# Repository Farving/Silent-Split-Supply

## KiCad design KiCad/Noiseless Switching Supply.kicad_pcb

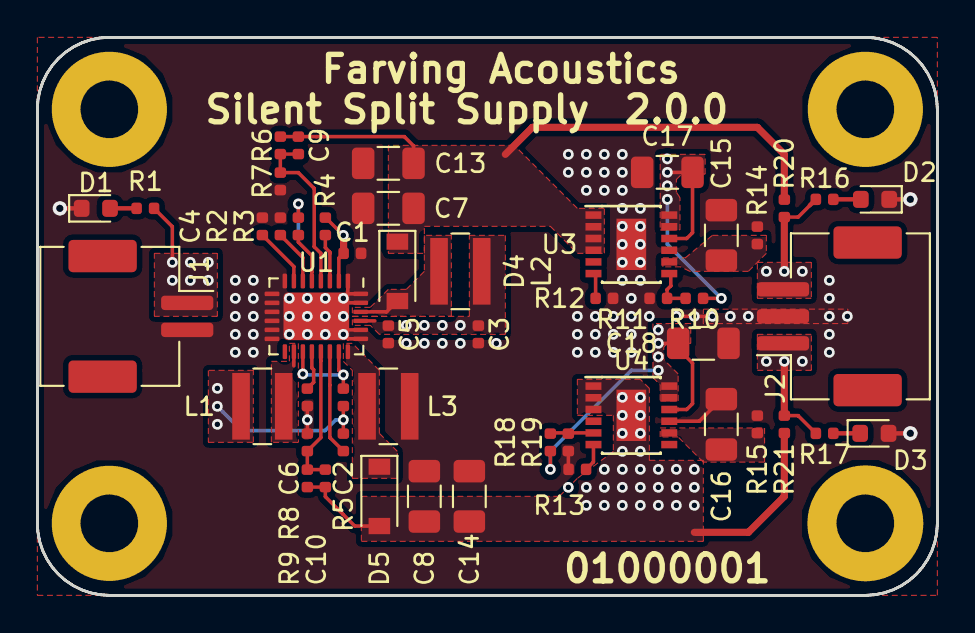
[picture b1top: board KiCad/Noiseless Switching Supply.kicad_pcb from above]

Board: 2 copper layers, 50.0 x 31.0 mm, 51 parts (0 on the bottom side), 27 nets.

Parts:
C1, C2: 1uF; C_0402_1005Metric
C3, C5: 2.2uF; C_0402_1005Metric
C4, C6: 100n; C_0402_1005Metric
C7, C8, C13, C14: 10u; C_1206_3216Metric
C9, C10: 10p; C_0402_1005Metric
C15, C16: 1u; C_1206_3216Metric
C17, C18: 10uF; C_1206_3216Metric
D1, D2, D3: LED_Small; LED_0603_1608Metric
D4, D5: D_Small; D_SOD-123
J1: JST S2B-ZR-SMA4-TF; JST_ZE_SM02B-ZESS-TBT_1x02-1MP_P1.50mm_Horizontal
J2: JST S3B-ZR-SMA4-TF; JST_ZE_SM03B-ZESS-TBT_1x03-1MP_P1.50mm_Horizontal
L1, L2, L3: 10u; L_Wuerth_MAPI-4030
PCB1: Board_Module; PCB_Board_50x31
R1, R16, R17: 1k; R_0402_1005Metric
R2: 82k; R_0402_1005Metric
R3, R4, R5: 100k; R_0402_1005Metric
R6, R9: 390k; R_0402_1005Metric
R7, R8, R11, R18: 18k; R_0402_1005Metric
R10, R19: 750k; R_0402_1005Metric
R12, R13, R20, R21: 0R; R_0402_1005Metric
R14, R15: 150k; R_0402_1005Metric
U1: LT8471; QFN-28-1EP_4x5mm_P0.5mm_EP2.65x3.65mm
U3: LT3045; MSOP-12-1EP_3x4mm_P0.65mm_EP1.65x2.85mm
U4: LT3094; MSOP-12-1EP_3x4mm_P0.65mm_EP1.65x2.85mm

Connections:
+15V: C17.1, J2.3, R10.1, R16.1, R20.1, U3.10, U3.11, U3.12
-15V: C18.2, J2.1, R17.2, R19.2, R21.1, U4.10, U4.11, U4.12
/VIN: C1.1, C2.1, C3.1, C5.1, J1.1, L1.1, L2.1, R1.1, R3.2, R4.2, R5.2, U1.2, U1.25
GND: C1.2, C3.2, C4.2, C5.2, C6.2, C7.2, C8.1, C13.2, C14.1, C15.2, C16.1, C17.2, C18.1, D1.1, D2.1, D3.2, J1.2, J2.2, L3.2, R2.2, R7.2, R8.1, R11.2, R12.2, R13.1, R14.2, R15.1, R18.1, U1.1, U1.8, U1.9, U1.10, U1.11, U1.12, U1.13, U1.14, U1.23, U1.24, U1.27, U1.28, U1.29, U3.9, U3.13, U4.9
unnamed: C2.2, U1.17, U1.21
unnamed: C4.1, U1.7
unnamed: C6.1, U1.18
unnamed: C9.2, R6.2, R7.1, U1.4
unnamed: C10.1, R8.2, R9.1, U1.19
unnamed: C15.1, R14.1, U3.8
unnamed: C16.2, R15.2, U4.8
unnamed: D1.2, R1.2
unnamed: D2.2, R16.2
unnamed: D3.1, R17.1
unnamed: D4.2, L2.2, U1.26
unnamed: D5.1, L3.1, U1.22
unnamed: L1.2, U1.16
unnamed: R2.1, U1.6
unnamed: R3.1, U1.5
unnamed: R4.1, U1.3
unnamed: R5.1, U1.20
unnamed: R10.2, R11.1, U3.7
unnamed: R12.1, U3.6
unnamed: R13.2, U4.6
unnamed: R18.2, R19.1, U4.5
VCC: C7.1, C9.1, C13.1, D4.1, R6.1, R20.2, U3.1, U3.2, U3.3, U3.4
VEE: C8.2, C10.2, C14.2, D5.2, R9.2, R21.2, U4.1, U4.2, U4.3, U4.13

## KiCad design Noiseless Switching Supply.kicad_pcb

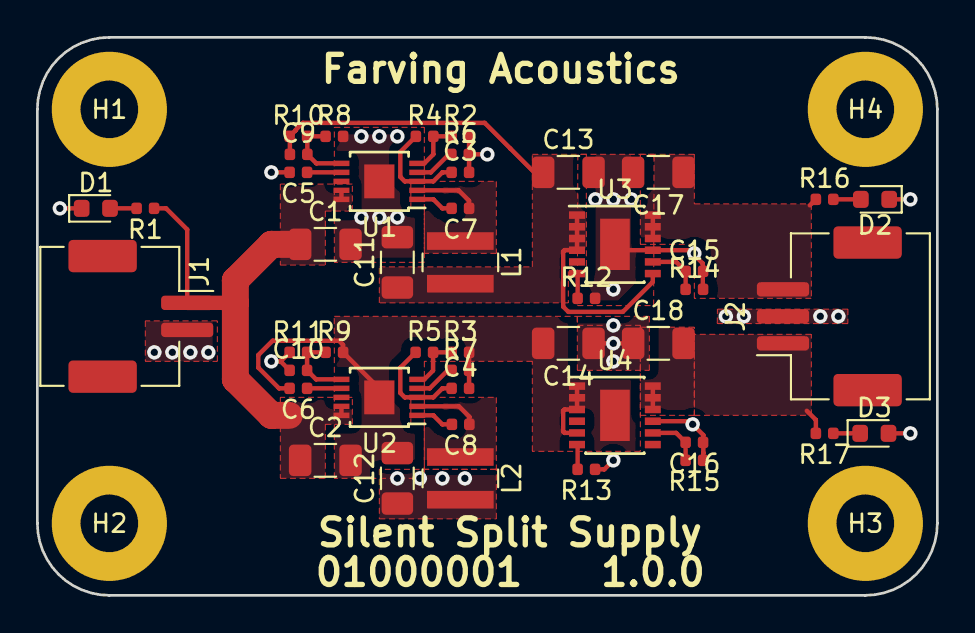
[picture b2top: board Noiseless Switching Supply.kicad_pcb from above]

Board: 2 copper layers, 50.0 x 31.0 mm, 50 parts (0 on the bottom side), 27 nets.

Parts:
C1, C2, C13, C14: 4.7uF; C_1206_3216Metric
C3, C4: 1uF; C_0402_1005Metric
C5, C6: 10nF; C_0402_1005Metric
C7, C8, C9, C10: 100nF; C_0402_1005Metric
C11, C12: 22uF; C_1206_3216Metric
C15, C16: 470nF; C_0402_1005Metric
C17, C18: 10uF; C_1206_3216Metric
D1, D2, D3: LED_Small; LED_0603_1608Metric
H1, H2, H3, H4: MountingHole_Pad; MountingHole_3.2mm_M3_Pad
J1: JST S2B-ZR-SMA4-TF; JST_ZE_SM02B-ZESS-TBT_1x02-1MP_P1.50mm_Horizontal
J2: JST S3B-ZR-SMA4-TF; JST_ZE_SM03B-ZESS-TBT_1x03-1MP_P1.50mm_Horizontal
L1, L2: L; L_Wuerth_MAPI-4020
R1, R16, R17: 1k; R_0402_1005Metric
R2, R3, R12, R13: 0R; R_0402_1005Metric
R4, R5: DNP; R_0402_1005Metric
R6, R7: 40.2k; R_0402_1005Metric
R8, R9, R10, R11: R_Small; R_0402_1005Metric
R14, R15: 150k; R_0402_1005Metric
U1, U2: LT8607; MSOP-10-1EP_3x3mm_P0.5mm_EP1.68x1.88mm
U3: LT3045; MSOP-12-1EP_3x4mm_P0.65mm_EP1.65x2.85mm
U4: LT3094; MSOP-12-1EP_3x4mm_P0.65mm_EP1.65x2.85mm

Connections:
+15V: C17.1, J2.3, R16.1, U3.10, U3.11, U3.12
-15V: C18.2, J2.1, R17.2, U4.10, U4.11, U4.12
/SW+: C7.1, L1.1, U1.2
/SW-: C8.1, L2.1, U2.2
/VIN: C1.1, C2.1, J1.1, R1.1, U1.9, U1.10, U2.9, U2.10
GND: C1.2, C3.2, C5.2, C10.1, C11.2, C12.1, C13.2, C14.1, C15.2, C16.1, C17.2, C18.1, D1.1, D2.1, D3.2, J1.2, J2.2, L2.2, R2.2, R6.2, R8.2, R11.1, R12.2, R13.1, R14.2, R15.1, U1.11, U3.9, U3.13, U4.9
unnamed: C3.1, R4.1, U1.3
unnamed: C4.1, R5.1, U2.3
unnamed: C5.1, U1.7
unnamed: C6.1, U2.7
unnamed: C7.2, U1.1
unnamed: C8.2, U2.1
unnamed: C9.2, R8.1, R10.2, U1.6
unnamed: C10.2, R9.1, R11.2, U2.6
unnamed: C15.1, R14.1, U3.8
unnamed: C16.2, R15.2, U4.8
unnamed: D1.2, R1.2
unnamed: D2.2, R16.2
unnamed: D3.1, R17.1
unnamed: R2.1, R4.2, U1.5
unnamed: R3.1, R5.2, U2.5
unnamed: R6.1, U1.4
unnamed: R7.1, U2.4
unnamed: R12.1, U3.6
unnamed: R13.2, U4.6
VCC: C9.1, C11.1, C13.1, L1.2, R10.1, U3.1, U3.2, U3.3, U3.4, U3.7
VEE: C2.2, C4.2, C6.2, C12.2, C14.2, R3.2, R7.2, R9.2, U2.11, U4.1, U4.2, U4.3, U4.5, U4.13

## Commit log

2018-11-13 Update gitignore
2018-11-13 Alpha release
2019-01-27 Add simulation for single buck solution
2019-02-01 Add Comments for rev 2
2019-05-07 2.0.0 Release
2019-06-11 Cleanup production and temporary files
2019-06-11 Update schematic
2019-06-11 Folder Restructuring
2019-07-05 Release 2.0.0
2019-07-05 Revert "Release 2.0.0"
    This reverts commit 205842f1cedd4a8ccdb19813492daaf6a9c54026.
2019-11-04 Add Simulation
